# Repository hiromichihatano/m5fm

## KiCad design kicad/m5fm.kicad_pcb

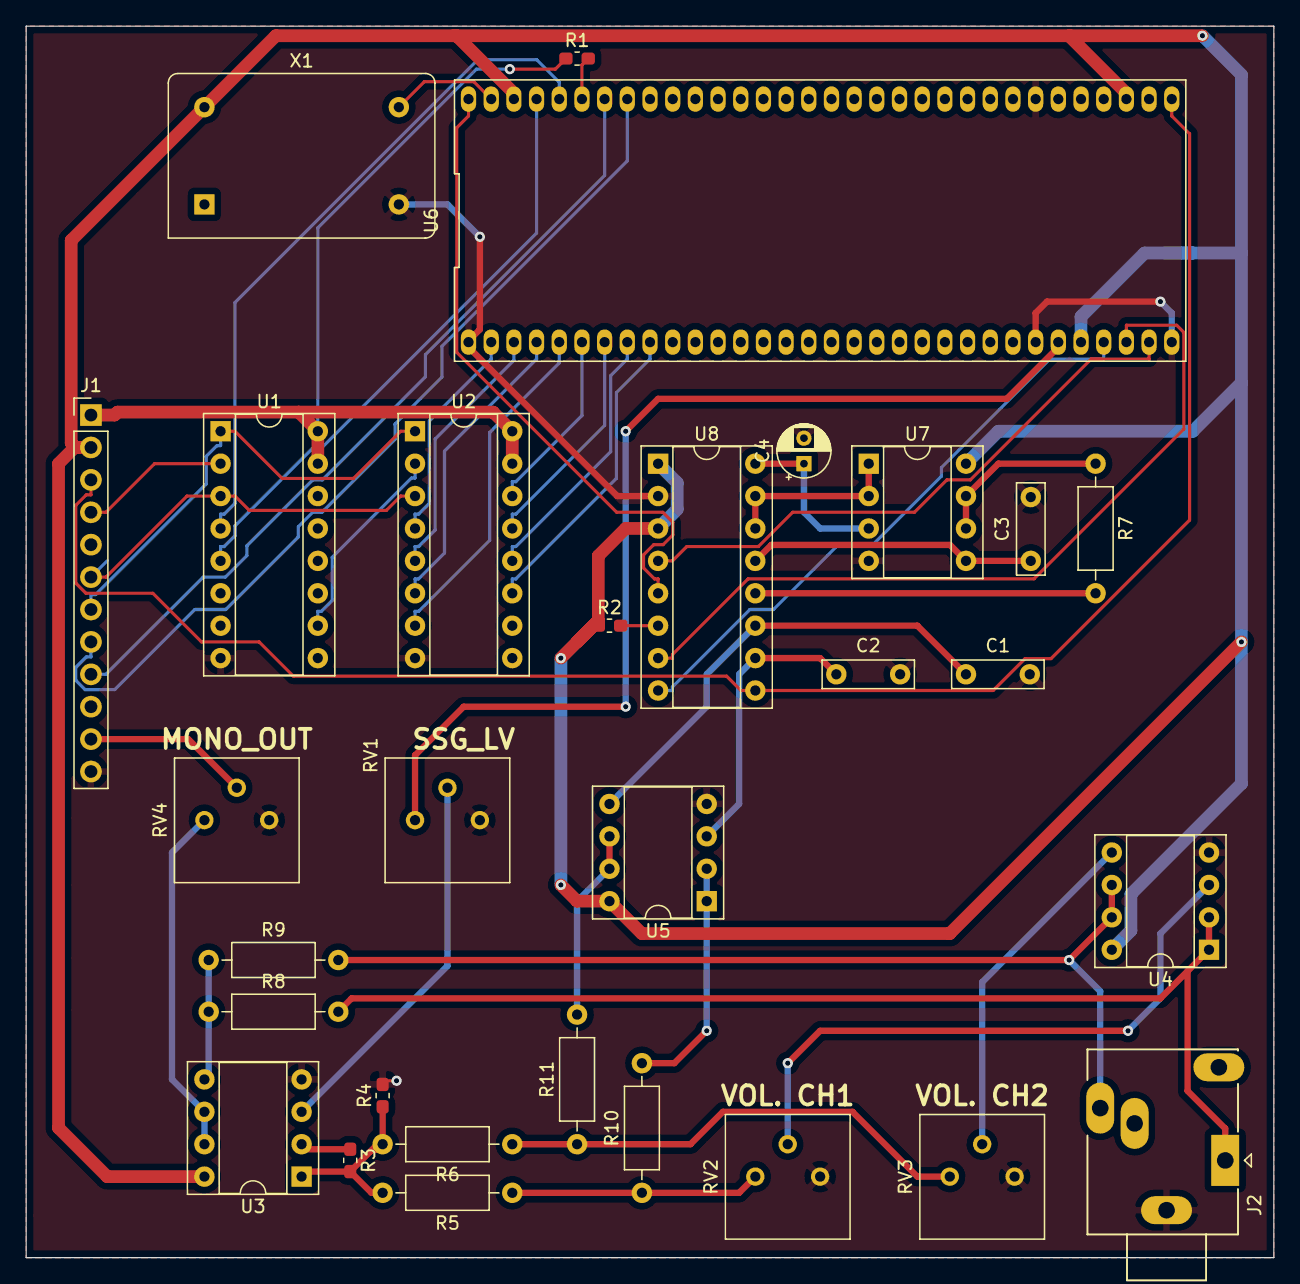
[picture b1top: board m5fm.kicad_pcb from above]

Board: 2 copper layers, 97.8 x 96.5 mm, 30 parts (0 on the bottom side), 49 nets.

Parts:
C1, C2: 2700PF; C_Rect_L7.0mm_W2.0mm_P5.00mm
C3: 68-33pF; C_Rect_L7.0mm_W2.0mm_P5.00mm
C4: 10u; CP_Radial_D4.0mm_P2.00mm
J1: Conn_01x12; PinHeader_1x12_P2.54mm_Vertical
J2: AudioJack3; Jack_3.5mm_Ledino_KB3SPRS_Horizontal
R1, R2: 1K; R_0603_1608Metric_Pad1.05x0.95mm_HandSolder
R3: 10K; R_0603_1608Metric_Pad1.05x0.95mm_HandSolder
R4: 4.7K; R_0603_1608Metric_Pad1.05x0.95mm_HandSolder
R5, R6, R8, R9, R10, R11: 10K; R_Axial_DIN0207_L6.3mm_D2.5mm_P10.16mm_Horizontal
R7: 33; R_Axial_DIN0207_L6.3mm_D2.5mm_P10.16mm_Horizontal
RV1, RV2, RV3, RV4: 10K; Potentiometer_Bourns_3386P_Vertical
U1, U2: 4094; DIP-16_W7.62mm_Socket
U3, U4, U5, U7: NJM4560; DIP-8_W7.62mm_Socket
U6: YM2608B; DIP-64_750_ELL
U8: YM3016-D; DIP-16_W7.62mm_Socket
X1: 8MHz; Oscillator_DIP-14

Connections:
+3V3: J1.1, R1.1, U1.15, U1.16, U2.15, U2.16
+5V: J1.2, R2.1, U3.8, U4.8, U5.8, U6.28, U6.35, U6.62, U7.8, U8.1, U8.3, X1.14
GND: C1.2, C2.2, C3.2, C4.2, J1.12, J2.S, R4.2, RV1.1, RV2.1, RV3.1, RV4.1, U1.8, U2.8, U3.4, U4.4, U5.4, U6.1, U6.26, U6.32, U6.39, U7.4, U8.2, X1.7
MONOSPK_OUT: J1.11, RV4.2
unnamed: C1.1, U5.5, U8.11
unnamed: C2.1, U5.3, U8.10
unnamed: C3.1, U7.5, U8.13
unnamed: C4.1, U7.3, U8.16
unnamed: J2.R, R9.2, U4.6, U4.7
unnamed: J2.T, R8.2, U4.1, U4.2
unnamed: R1.2, U6.59
unnamed: R2.2, U8.6
unnamed: R3.1, U3.2
unnamed: R3.2, R4.1, R5.2, R6.2, U3.1
unnamed: R7.1, U7.6, U7.7
unnamed: R7.2, U8.12
unnamed: R8.1, R9.1, U3.5
unnamed: R5.1, R10.1, RV2.3
unnamed: R10.2, U5.1, U5.2
unnamed: R6.1, R11.1, RV3.3
unnamed: R11.2, U5.6, U5.7
unnamed: RV1.2, U3.3
unnamed: RV1.3, U6.27
unnamed: RV2.2, U4.3
unnamed: RV3.2, U4.5
unnamed: RV4.3, U3.6, U3.7
unnamed: U1.4, U6.60
unnamed: U1.5, U6.61
unnamed: U1.10, U2.2
unnamed: U2.4, U6.2
unnamed: U2.5, U6.3
unnamed: U2.6, U6.4
unnamed: U2.7, U6.5
unnamed: U2.11, U6.9
unnamed: U2.12, U6.8
unnamed: U2.13, U6.7
unnamed: U2.14, U6.6
unnamed: U6.29, U8.8
unnamed: U6.30, U8.7
unnamed: U6.31, U8.4
unnamed: U6.63, X1.8
unnamed: U6.64, U8.5
unnamed: U7.1, U7.2, U8.14, U8.15
RST: J1.3, U6.33, U8.9
SPI_MOSI: J1.4, U1.2
SPI_SCK: J1.6, U1.3, U2.3
SPI_SS: J1.7, U1.1, U2.1
YM_CS: J1.8, U6.57
YM_WR: J1.9, U6.58

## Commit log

2020-01-26 Config PlatformIO
2020-01-26 Add baud rate
2020-01-26 Add SSG lowlayer drive functions.
2020-01-27 Split YM_LL file
2020-01-31 Remove ssg bug and add test pipo sound
2020-02-01 Add FM block empty functions
2020-02-02 Implement some fm_ll functions.
2020-02-10 Add getting FM Parameter Addr function.
2020-02-11 Add 3 functions
2020-02-11 Add FM_ll implementations
2020-02-11 Add basic FM_ll functions
2020-02-11 Change push btn then note on
2020-02-28 Add kicad ignores
2020-02-28 Add kicad and tepra files
